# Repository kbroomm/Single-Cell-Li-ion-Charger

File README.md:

# Li Charger

KiCad PCB design for a single-cell lithium-ion battery charger, with a 5V USB-C input and 10-LED charge level indicator.

## Features

- **BQ24092** linear charger IC (Texas Instruments)
- **LM3914** dot/bar display driver for charge indication
- USB-C power input
- JST battery connector

## Project structure

```
├── hardware/              KiCad schematic, PCB, and custom libraries
│   ├── Li Charger.kicad_pro
│   ├── Li Charger.kicad_sch
│   ├── Li Charger.kicad_pcb
│   └── libs/              Custom symbol and footprint imports
├── manufacturing/
│   └── gerbers/           Fabrication outputs (Gerber + drill files)
├── datasheets/        	   Component reference PDFs
├── 3D models/             Component models not included in standard libs
```
## Manufacturing

Gerber and drill files for PCB fabrication are in `manufacturing/gerbers/`.

## Datasheets

| Part     | Document                                      |
|----------|-----------------------------------------------|
| BQ24092  | [docs/datasheets/bq24092.pdf](docs/datasheets/bq24092.pdf) |
| LM3914   | [docs/datasheets/lm3914.pdf](docs/datasheets/lm3914.pdf)   |

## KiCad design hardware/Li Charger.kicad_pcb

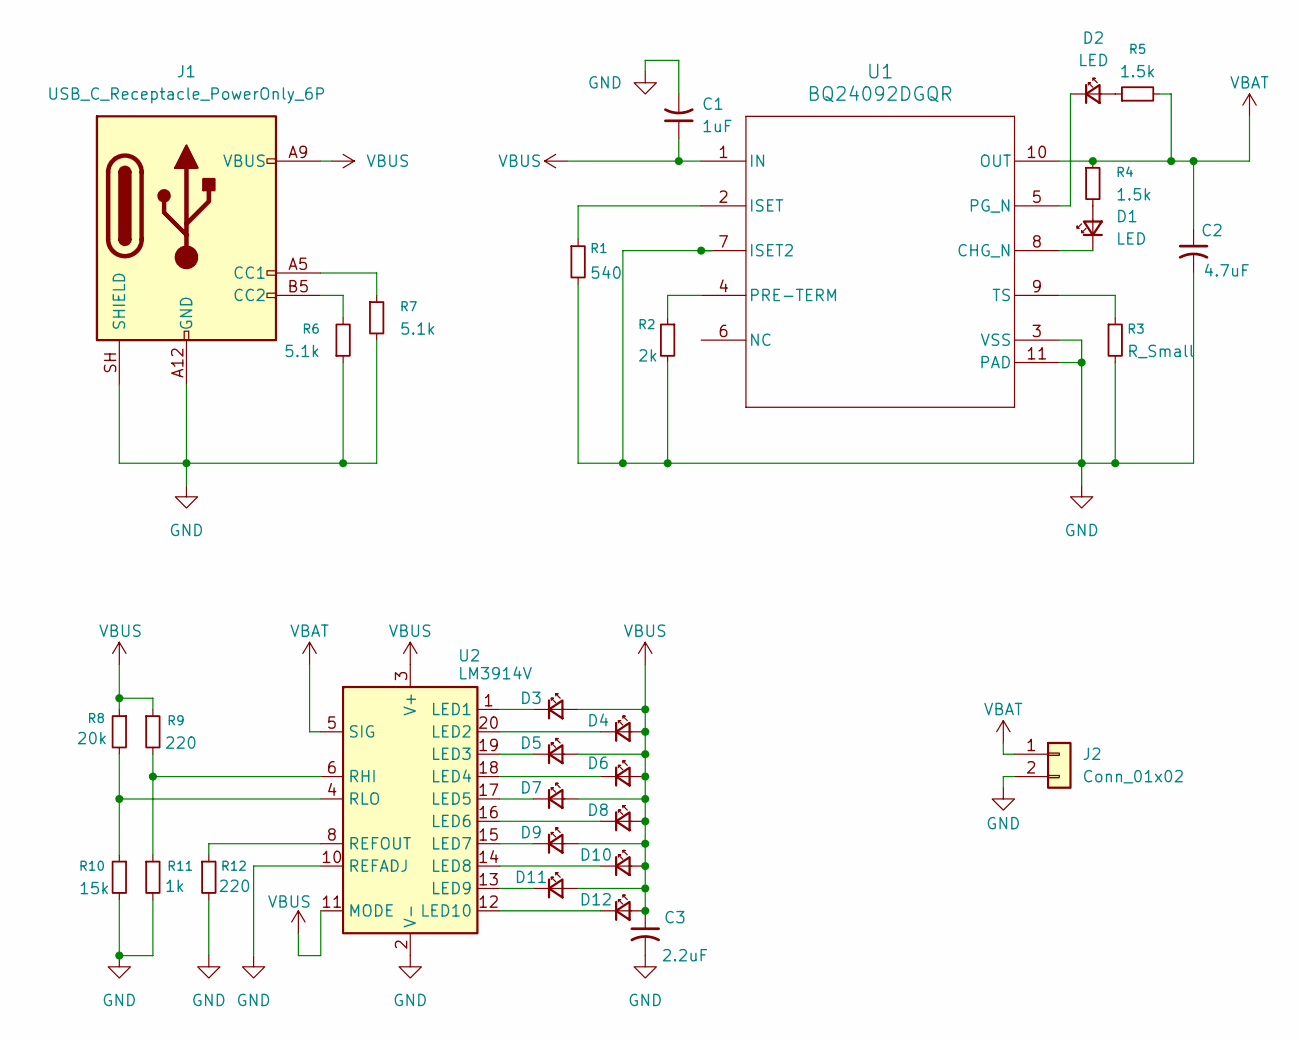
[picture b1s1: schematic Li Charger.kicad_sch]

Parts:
C1: 1uF; C_0805_2012Metric
C2: 4.7uF; C_0805_2012Metric
C3: 2.2uF; C_0805_2012Metric
D1, D2: LED; LED_0805_2012Metric
D3, D4, D5, D6, D7, D8, D9, D10, D11, D12: LED_Small; LED_0805_2012Metric
J1: USB_C_Receptacle_PowerOnly_6P; USB_C_Receptacle_HRO_TYPE-C-31-M-12
J2: Conn_01x02; JST_JWPF_B02B-JWPF-SK-R_1x02_P2.00mm_Vertical
R1: 540; R_0805_2012Metric
R2: 2k; R_0805_2012Metric
R3: R_Small; R_0805_2012Metric
R4, R5: 1.5k; R_0805_2012Metric
R6, R7: 5.1k; R_0805_2012Metric
R8: 20k; R_0805_2012Metric
R9, R12: 220; R_0805_2012Metric
R10: 15k; R_0805_2012Metric
R11: 1k; R_0805_2012Metric
U1: BQ24092DGQR; HVSSOP-10-1EP_3x3mm_P0.5mm_EP1.83x1.89mm
U2: LM3914V; PLCC-20

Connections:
GND: C1.2, C2.2, C3.2, J1.A12 (GND), J1.B12 (GND), J1.SH (SHIELD), J2.2, R1.2, R2.2, R3.2, R6.1, R7.2, R10.2, R11.2, R12.2, U1.3 (VSS), U1.7 (ISET2), U1.11 (PAD), U2.2 (V-), U2.10 (REFADJ); also elsewhere on the board
unnamed: D1.2 (A), R4.2
unnamed: D1.1 (K), U1.8 (CHG_N)
unnamed: D2.2 (A), R5.1
unnamed: D2.1 (K), U1.5 (PG_N)
unnamed: D3.1 (K), U2.1 (LED1)
unnamed: D4.1 (K), U2.20 (LED2)
unnamed: D5.1 (K), U2.19 (LED3)
unnamed: D6.1 (K), U2.18 (LED4)
unnamed: D7.1 (K), U2.17 (LED5)
unnamed: D8.1 (K), U2.16 (LED6)
unnamed: D9.1 (K), U2.15 (LED7)
unnamed: D10.1 (K), U2.14 (LED8)
unnamed: D11.1 (K), U2.13 (LED9)
unnamed: D12.1 (K), U2.12 (LED10)
unnamed: J1.A5 (CC1), R7.1
unnamed: J1.B5 (CC2), R6.2
unnamed: R1.1, U1.2 (ISET)
unnamed: R2.1, U1.4 (PRE-TERM)
unnamed: R3.1, U1.9 (TS)
unnamed: R12.1, U2.8 (REFOUT)
unnamed: R9.2, R11.1, U2.6 (RHI)
unnamed: R8.2, R10.1, U2.4 (RLO)
VBAT: C2.1, J2.1, R4.1, R5.2, U1.10 (OUT), U2.5 (SIG); also elsewhere on the board
VBUS: C1.1, C3.1, D3.2 (A), D4.2 (A), D5.2 (A), D6.2 (A), D7.2 (A), D8.2 (A), D9.2 (A), D10.2 (A), D11.2 (A), D12.2 (A), J1.A9 (VBUS), J1.B9 (VBUS), R8.1, R9.1, U1.1 (IN), U2.3 (V+), U2.11 (MODE); also elsewhere on the board

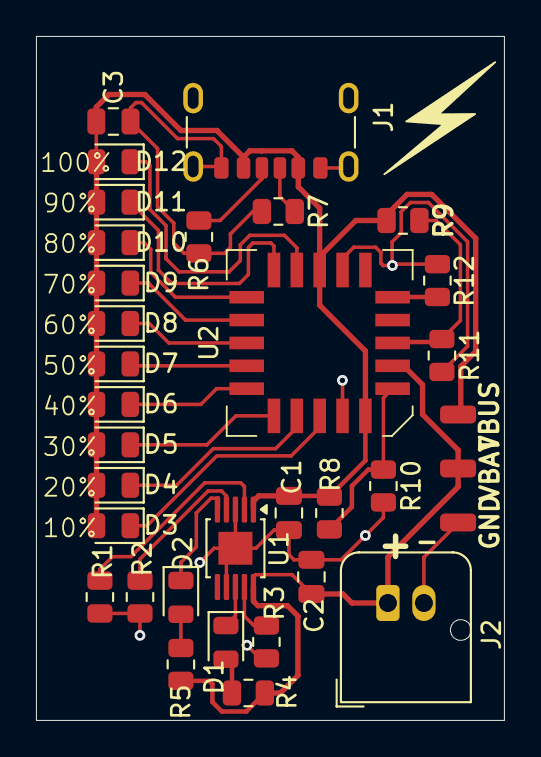
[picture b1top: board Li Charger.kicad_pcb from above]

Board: 2 copper layers, 26.0 x 38.0 mm, 34 parts (0 on the bottom side), 25 nets.

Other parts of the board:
GND: SolderWirePad_1x01_SMD_1x2mm
VBAT: SolderWirePad_1x01_SMD_1x2mm
VBUS: SolderWirePad_1x01_SMD_1x2mm

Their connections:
GND: GND.1; also elsewhere on the board
VBAT: VBAT.1; also elsewhere on the board
VBUS: VBUS.1; also elsewhere on the board

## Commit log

2026-06-13 Make Repo Public
2026-06-13 Schematic Value Update
